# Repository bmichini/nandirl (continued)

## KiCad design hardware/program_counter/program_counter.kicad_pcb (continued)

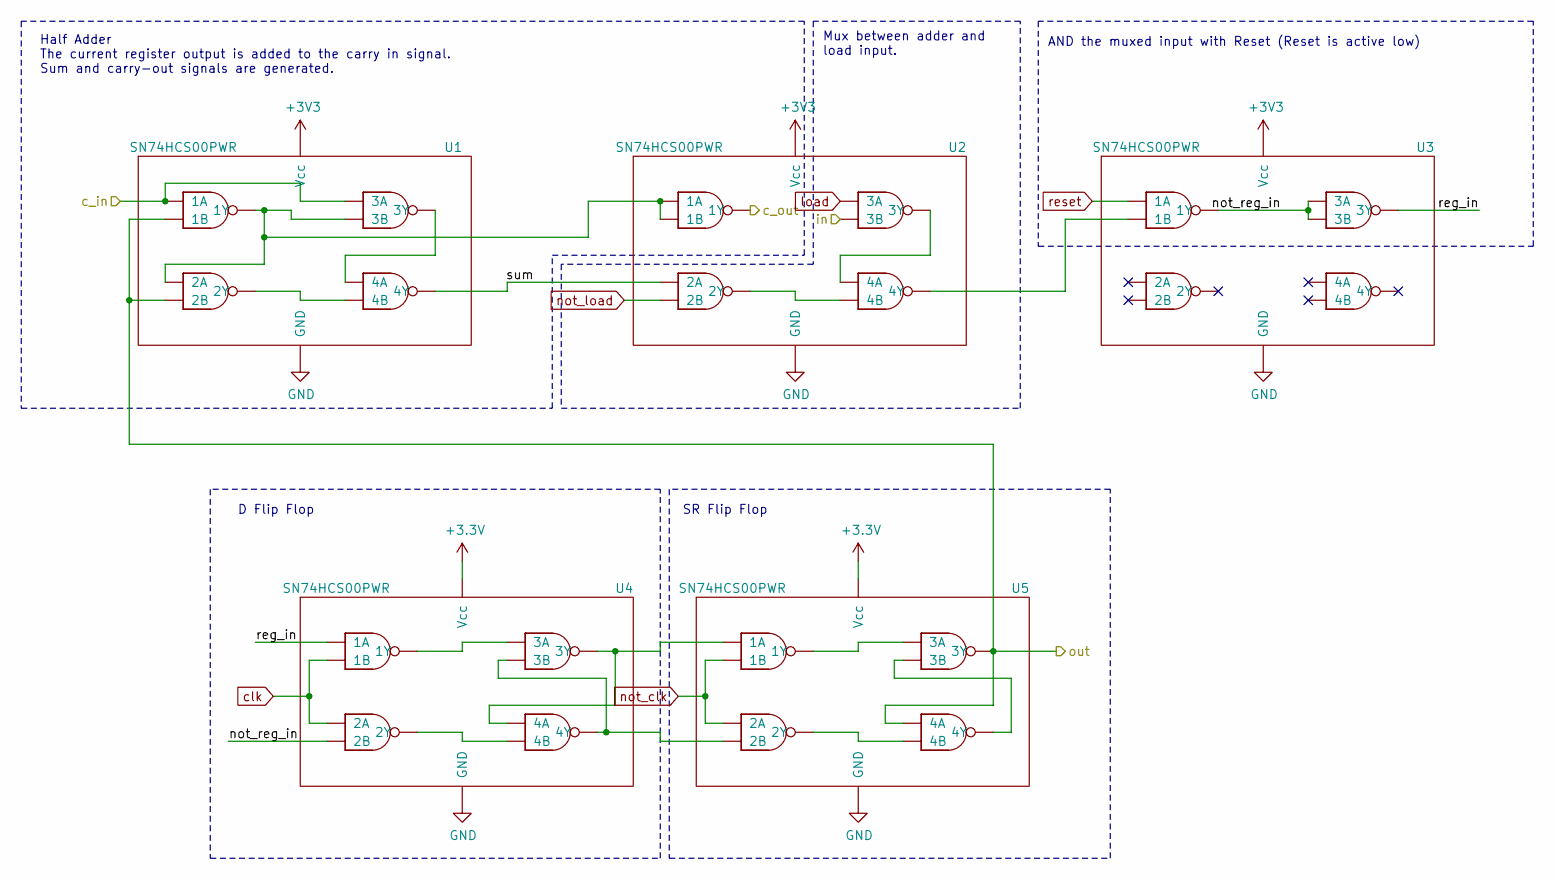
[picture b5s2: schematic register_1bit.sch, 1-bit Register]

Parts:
U1, U2, U3, U4, U5: SN74HCS00PWR; TSSOP-14_4.4x5mm_P0.65mm; Digikey PN 296-SN74HCS00PWRCT-ND

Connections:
/Bit 0/not_reg_in: U3.3 (1Y), U3.9 (3A), U3.10 (3B), U4.5 (2B)
/Bit 0/reg_in: U3.8 (3Y), U4.1 (1A)
/Bit 0/sum: U1.11 (4Y), U2.4 (2A)
/sheet5EB6EF30/c_in: U2.3 (1Y); also elsewhere on the board
GND: U1.7 (GND), U2.7 (GND), U3.7 (GND), U4.7 (GND), U5.7 (GND); also elsewhere on the board
unnamed: U1.3 (1Y), U1.4 (2A), U1.10 (3B), U2.1 (1A), U2.2 (1B)
unnamed: U1.8 (3Y), U1.12 (4A)
unnamed: U1.6 (2Y), U1.13 (4B)
unnamed: U2.11 (4Y), U3.2 (1B)
unnamed: U2.8 (3Y), U2.12 (4A)
unnamed: U2.6 (2Y), U2.13 (4B)
unnamed: U4.3 (1Y), U4.9 (3A)
unnamed: U4.10 (3B), U4.11 (4Y), U5.5 (2B)
unnamed: U4.8 (3Y), U4.12 (4A), U5.1 (1A)
unnamed: U4.6 (2Y), U4.13 (4B)
unnamed: U5.3 (1Y), U5.9 (3A)
unnamed: U5.10 (3B), U5.11 (4Y)
unnamed: U5.6 (2Y), U5.13 (4B)
clk: U4.2 (1B), U4.4 (2A); also elsewhere on the board
in0: U2.10 (3B); also elsewhere on the board
inc: U1.1 (1A), U1.9 (3A); also elsewhere on the board
load: U2.9 (3A); also elsewhere on the board
not_clk: U5.2 (1B), U5.4 (2A); also elsewhere on the board
not_load: U2.5 (2B); also elsewhere on the board
out0: U1.2 (1B), U1.5 (2B), U5.8 (3Y), U5.12 (4A); also elsewhere on the board
reset: U3.1 (1A); also elsewhere on the board

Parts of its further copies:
U6, U7, U8, U9, U10, U11, U12, U13, U14, U15, U16, U17, U18, U19, U20, U21, U22, U23, U24, U25, U26, U27, U28, U29, U30, U31, U32, U33, U34, U35, U36, U37, U38, U39, U40, U41, U42, U43, U44, U45, U46, U47, U48, U49, U50, U51, U52, U53, U54, U55, U56, U57, U58, U59, U60, U61, U62, U63, U64, U65, U66, U67, U68, U69, U70, U71, U72, U73, U74, U75: SN74HCS00PWR; TSSOP-14_4.4x5mm_P0.65mm; Digikey PN 296-SN74HCS00PWRCT-ND

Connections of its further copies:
/sheet5EB6EF30/c_in: U71.1 (1A), U71.9 (3A); also elsewhere on the board
/sheet5EB6EF30/not_reg_in: U73.3 (1Y), U73.9 (3A), U73.10 (3B), U74.5 (2B)
/sheet5EB6EF30/reg_in: U73.8 (3Y), U74.1 (1A)
/sheet5EB6EF30/sum: U71.11 (4Y), U72.4 (2A)
/sheet5EBCE384/c_in: U66.1 (1A), U66.9 (3A), U72.3 (1Y)
/sheet5EBCE384/not_reg_in: U68.3 (1Y), U68.9 (3A), U68.10 (3B), U69.5 (2B)
/sheet5EBCE384/reg_in: U68.8 (3Y), U69.1 (1A)
/sheet5EBCE384/sum: U66.11 (4Y), U67.4 (2A)
/sheet5EBD798B/c_in: U61.1 (1A), U61.9 (3A), U67.3 (1Y)
/sheet5EBD798B/not_reg_in: U63.3 (1Y), U63.9 (3A), U63.10 (3B), U64.5 (2B)
/sheet5EBD798B/reg_in: U63.8 (3Y), U64.1 (1A)
/sheet5EBD798B/sum: U61.11 (4Y), U62.4 (2A)
/sheet5EBD798C/c_in: U56.1 (1A), U56.9 (3A), U62.3 (1Y)
/sheet5EBD798C/not_reg_in: U58.3 (1Y), U58.9 (3A), U58.10 (3B), U59.5 (2B)
/sheet5EBD798C/reg_in: U58.8 (3Y), U59.1 (1A)
/sheet5EBD798C/sum: U56.11 (4Y), U57.4 (2A)
/sheet5EBF7D34/c_in: U51.1 (1A), U51.9 (3A), U57.3 (1Y)
/sheet5EBF7D34/not_reg_in: U53.3 (1Y), U53.9 (3A), U53.10 (3B), U54.5 (2B)
/sheet5EBF7D34/reg_in: U53.8 (3Y), U54.1 (1A)
/sheet5EBF7D34/sum: U51.11 (4Y), U52.4 (2A)
/sheet5EBF7D35/c_in: U46.1 (1A), U46.9 (3A), U52.3 (1Y)
/sheet5EBF7D35/not_reg_in: U48.3 (1Y), U48.9 (3A), U48.10 (3B), U49.5 (2B)
/sheet5EBF7D35/reg_in: U48.8 (3Y), U49.1 (1A)
/sheet5EBF7D35/sum: U46.11 (4Y), U47.4 (2A)
/sheet5EBF7D36/c_in: U41.1 (1A), U41.9 (3A), U47.3 (1Y)
/sheet5EBF7D36/not_reg_in: U43.3 (1Y), U43.9 (3A), U43.10 (3B), U44.5 (2B)
/sheet5EBF7D36/reg_in: U43.8 (3Y), U44.1 (1A)
/sheet5EBF7D36/sum: U41.11 (4Y), U42.4 (2A)
/sheet5EBF7D37/c_in: U36.1 (1A), U36.9 (3A), U42.3 (1Y)
/sheet5EBF7D37/not_reg_in: U38.3 (1Y), U38.9 (3A), U38.10 (3B), U39.5 (2B)
/sheet5EBF7D37/reg_in: U38.8 (3Y), U39.1 (1A)
/sheet5EBF7D37/sum: U36.11 (4Y), U37.4 (2A)
/sheet5EC1DCDE/c_in: U31.1 (1A), U31.9 (3A), U37.3 (1Y)
/sheet5EC1DCDE/not_reg_in: U33.3 (1Y), U33.9 (3A), U33.10 (3B), U34.5 (2B)
/sheet5EC1DCDE/reg_in: U33.8 (3Y), U34.1 (1A)
/sheet5EC1DCDE/sum: U31.11 (4Y), U32.4 (2A)
/sheet5EC1DCDF/c_in: U26.1 (1A), U26.9 (3A), U32.3 (1Y)
/sheet5EC1DCDF/not_reg_in: U28.3 (1Y), U28.9 (3A), U28.10 (3B), U29.5 (2B)
/sheet5EC1DCDF/reg_in: U28.8 (3Y), U29.1 (1A)
/sheet5EC1DCDF/sum: U26.11 (4Y), U27.4 (2A)
/sheet5EC1DCE0/c_in: U21.1 (1A), U21.9 (3A), U27.3 (1Y)
/sheet5EC1DCE0/not_reg_in: U23.3 (1Y), U23.9 (3A), U23.10 (3B), U24.5 (2B)
/sheet5EC1DCE0/reg_in: U23.8 (3Y), U24.1 (1A)
/sheet5EC1DCE0/sum: U21.11 (4Y), U22.4 (2A)
/sheet5EC1DCE1/c_in: U16.1 (1A), U16.9 (3A), U22.3 (1Y)
/sheet5EC1DCE1/not_reg_in: U18.3 (1Y), U18.9 (3A), U18.10 (3B), U19.5 (2B)
/sheet5EC1DCE1/reg_in: U18.8 (3Y), U19.1 (1A)
/sheet5EC1DCE1/sum: U16.11 (4Y), U17.4 (2A)
/sheet5EC1DCE2/c_in: U11.1 (1A), U11.9 (3A), U17.3 (1Y)
/sheet5EC1DCE2/not_reg_in: U13.3 (1Y), U13.9 (3A), U13.10 (3B), U14.5 (2B)
/sheet5EC1DCE2/reg_in: U13.8 (3Y), U14.1 (1A)
/sheet5EC1DCE2/sum: U11.11 (4Y), U12.4 (2A)
/sheet5EC1DCE3/c_in: U6.1 (1A), U6.9 (3A), U12.3 (1Y)
/sheet5EC1DCE3/c_out: U7.3 (1Y)
/sheet5EC1DCE3/not_reg_in: U8.3 (1Y), U8.9 (3A), U8.10 (3B), U9.5 (2B)
/sheet5EC1DCE3/reg_in: U8.8 (3Y), U9.1 (1A)
/sheet5EC1DCE3/sum: U6.11 (4Y), U7.4 (2A)
GND: U6.7 (GND), U7.7 (GND), U8.7 (GND), U9.7 (GND), U10.7 (GND), U11.7 (GND), U12.7 (GND), U13.7 (GND), U14.7 (GND), U15.7 (GND), U16.7 (GND), U17.7 (GND), U18.7 (GND), U19.7 (GND), U20.7 (GND), U21.7 (GND), U22.7 (GND), U23.7 (GND), U24.7 (GND), U25.7 (GND), U26.7 (GND), U27.7 (GND), U28.7 (GND), U29.7 (GND), U30.7 (GND), U31.7 (GND), U32.7 (GND), U33.7 (GND), U34.7 (GND), U35.7 (GND), U36.7 (GND), U37.7 (GND), U38.7 (GND), U39.7 (GND), U40.7 (GND), U41.7 (GND), U42.7 (GND), U43.7 (GND), U44.7 (GND), U45.7 (GND), U46.7 (GND), U47.7 (GND), U48.7 (GND), U49.7 (GND), U50.7 (GND), U51.7 (GND), U52.7 (GND), U53.7 (GND), U54.7 (GND), U55.7 (GND), U56.7 (GND), U57.7 (GND), U58.7 (GND), U59.7 (GND), U60.7 (GND), U61.7 (GND), U62.7 (GND), U63.7 (GND), U64.7 (GND), U65.7 (GND), U66.7 (GND), U67.7 (GND), U68.7 (GND), U69.7 (GND), U70.7 (GND), U71.7 (GND), U72.7 (GND), U73.7 (GND), U74.7 (GND), U75.7 (GND); also elsewhere on the board
unnamed: U6.3 (1Y), U6.4 (2A), U6.10 (3B), U7.1 (1A), U7.2 (1B)
unnamed: U6.8 (3Y), U6.12 (4A)
unnamed: U6.6 (2Y), U6.13 (4B)
unnamed: U7.11 (4Y), U8.2 (1B)
unnamed: U7.8 (3Y), U7.12 (4A)
unnamed: U7.6 (2Y), U7.13 (4B)
unnamed: U9.3 (1Y), U9.9 (3A)
unnamed: U9.6 (2Y), U9.13 (4B)
unnamed: U9.8 (3Y), U9.12 (4A), U10.1 (1A)
unnamed: U10.3 (1Y), U10.9 (3A)
unnamed: U9.10 (3B), U9.11 (4Y), U10.5 (2B)
unnamed: U10.10 (3B), U10.11 (4Y)
unnamed: U10.6 (2Y), U10.13 (4B)
unnamed: U11.3 (1Y), U11.4 (2A), U11.10 (3B), U12.1 (1A), U12.2 (1B)
unnamed: U11.8 (3Y), U11.12 (4A)
unnamed: U11.6 (2Y), U11.13 (4B)
unnamed: U12.11 (4Y), U13.2 (1B)
unnamed: U12.8 (3Y), U12.12 (4A)
unnamed: U12.6 (2Y), U12.13 (4B)
unnamed: U14.3 (1Y), U14.9 (3A)
unnamed: U14.10 (3B), U14.11 (4Y), U15.5 (2B)
unnamed: U14.8 (3Y), U14.12 (4A), U15.1 (1A)
unnamed: U14.6 (2Y), U14.13 (4B)
unnamed: U15.3 (1Y), U15.9 (3A)
unnamed: U15.10 (3B), U15.11 (4Y)
unnamed: U15.6 (2Y), U15.13 (4B)
unnamed: U16.3 (1Y), U16.4 (2A), U16.10 (3B), U17.1 (1A), U17.2 (1B)
unnamed: U16.8 (3Y), U16.12 (4A)
unnamed: U16.6 (2Y), U16.13 (4B)
unnamed: U17.11 (4Y), U18.2 (1B)
unnamed: U17.8 (3Y), U17.12 (4A)
unnamed: U17.6 (2Y), U17.13 (4B)
unnamed: U19.3 (1Y), U19.9 (3A)
unnamed: U19.10 (3B), U19.11 (4Y), U20.5 (2B)
unnamed: U19.8 (3Y), U19.12 (4A), U20.1 (1A)
unnamed: U19.6 (2Y), U19.13 (4B)
unnamed: U20.3 (1Y), U20.9 (3A)
unnamed: U20.10 (3B), U20.11 (4Y)
unnamed: U20.6 (2Y), U20.13 (4B)
unnamed: U21.3 (1Y), U21.4 (2A), U21.10 (3B), U22.1 (1A), U22.2 (1B)
unnamed: U21.8 (3Y), U21.12 (4A)
unnamed: U21.6 (2Y), U21.13 (4B)
unnamed: U22.11 (4Y), U23.2 (1B)
unnamed: U22.8 (3Y), U22.12 (4A)
unnamed: U22.6 (2Y), U22.13 (4B)
unnamed: U24.3 (1Y), U24.9 (3A)
unnamed: U24.10 (3B), U24.11 (4Y), U25.5 (2B)
unnamed: U24.8 (3Y), U24.12 (4A), U25.1 (1A)
unnamed: U24.6 (2Y), U24.13 (4B)
unnamed: U25.3 (1Y), U25.9 (3A)
unnamed: U25.10 (3B), U25.11 (4Y)
unnamed: U25.6 (2Y), U25.13 (4B)
unnamed: U26.3 (1Y), U26.4 (2A), U26.10 (3B), U27.1 (1A), U27.2 (1B)
unnamed: U26.8 (3Y), U26.12 (4A)
unnamed: U26.6 (2Y), U26.13 (4B)
unnamed: U27.11 (4Y), U28.2 (1B)
unnamed: U27.8 (3Y), U27.12 (4A)
unnamed: U27.6 (2Y), U27.13 (4B)
unnamed: U29.3 (1Y), U29.9 (3A)
unnamed: U29.10 (3B), U29.11 (4Y), U30.5 (2B)
unnamed: U29.8 (3Y), U29.12 (4A), U30.1 (1A)
unnamed: U29.6 (2Y), U29.13 (4B)
unnamed: U30.3 (1Y), U30.9 (3A)
unnamed: U30.10 (3B), U30.11 (4Y)
unnamed: U30.6 (2Y), U30.13 (4B)
unnamed: U31.3 (1Y), U31.4 (2A), U31.10 (3B), U32.1 (1A), U32.2 (1B)
unnamed: U31.8 (3Y), U31.12 (4A)
unnamed: U31.6 (2Y), U31.13 (4B)
unnamed: U32.11 (4Y), U33.2 (1B)
unnamed: U32.8 (3Y), U32.12 (4A)
unnamed: U32.6 (2Y), U32.13 (4B)
unnamed: U34.3 (1Y), U34.9 (3A)
unnamed: U34.10 (3B), U34.11 (4Y), U35.5 (2B)
unnamed: U34.8 (3Y), U34.12 (4A), U35.1 (1A)
unnamed: U34.6 (2Y), U34.13 (4B)
unnamed: U35.3 (1Y), U35.9 (3A)
unnamed: U35.10 (3B), U35.11 (4Y)
unnamed: U35.6 (2Y), U35.13 (4B)
unnamed: U36.3 (1Y), U36.4 (2A), U36.10 (3B), U37.1 (1A), U37.2 (1B)
unnamed: U36.8 (3Y), U36.12 (4A)
unnamed: U36.6 (2Y), U36.13 (4B)
unnamed: U37.11 (4Y), U38.2 (1B)
unnamed: U37.8 (3Y), U37.12 (4A)
unnamed: U37.6 (2Y), U37.13 (4B)
unnamed: U39.3 (1Y), U39.9 (3A)
unnamed: U39.10 (3B), U39.11 (4Y), U40.5 (2B)
unnamed: U39.8 (3Y), U39.12 (4A), U40.1 (1A)
unnamed: U39.6 (2Y), U39.13 (4B)
unnamed: U40.3 (1Y), U40.9 (3A)
unnamed: U40.10 (3B), U40.11 (4Y)
unnamed: U40.6 (2Y), U40.13 (4B)
unnamed: U41.3 (1Y), U41.4 (2A), U41.10 (3B), U42.1 (1A), U42.2 (1B)
unnamed: U41.8 (3Y), U41.12 (4A)
unnamed: U41.6 (2Y), U41.13 (4B)
unnamed: U42.11 (4Y), U43.2 (1B)
unnamed: U42.8 (3Y), U42.12 (4A)
unnamed: U42.6 (2Y), U42.13 (4B)
unnamed: U44.3 (1Y), U44.9 (3A)
unnamed: U44.10 (3B), U44.11 (4Y), U45.5 (2B)
unnamed: U44.8 (3Y), U44.12 (4A), U45.1 (1A)
unnamed: U44.6 (2Y), U44.13 (4B)
unnamed: U45.3 (1Y), U45.9 (3A)
unnamed: U45.10 (3B), U45.11 (4Y)
unnamed: U45.6 (2Y), U45.13 (4B)
unnamed: U46.3 (1Y), U46.4 (2A), U46.10 (3B), U47.1 (1A), U47.2 (1B)
unnamed: U46.8 (3Y), U46.12 (4A)
unnamed: U46.6 (2Y), U46.13 (4B)
unnamed: U47.11 (4Y), U48.2 (1B)
unnamed: U47.8 (3Y), U47.12 (4A)
unnamed: U47.6 (2Y), U47.13 (4B)
unnamed: U49.3 (1Y), U49.9 (3A)
unnamed: U49.10 (3B), U49.11 (4Y), U50.5 (2B)
unnamed: U49.8 (3Y), U49.12 (4A), U50.1 (1A)
unnamed: U49.6 (2Y), U49.13 (4B)
unnamed: U50.3 (1Y), U50.9 (3A)
unnamed: U50.10 (3B), U50.11 (4Y)
unnamed: U50.6 (2Y), U50.13 (4B)
unnamed: U51.3 (1Y), U51.4 (2A), U51.10 (3B), U52.1 (1A), U52.2 (1B)
unnamed: U51.8 (3Y), U51.12 (4A)
unnamed: U51.6 (2Y), U51.13 (4B)
unnamed: U52.11 (4Y), U53.2 (1B)
unnamed: U52.8 (3Y), U52.12 (4A)
unnamed: U52.6 (2Y), U52.13 (4B)
unnamed: U54.3 (1Y), U54.9 (3A)
unnamed: U54.10 (3B), U54.11 (4Y), U55.5 (2B)
unnamed: U54.8 (3Y), U54.12 (4A), U55.1 (1A)
unnamed: U54.6 (2Y), U54.13 (4B)
unnamed: U55.3 (1Y), U55.9 (3A)
unnamed: U55.10 (3B), U55.11 (4Y)
unnamed: U55.6 (2Y), U55.13 (4B)
unnamed: U56.3 (1Y), U56.4 (2A), U56.10 (3B), U57.1 (1A), U57.2 (1B)
unnamed: U56.8 (3Y), U56.12 (4A)
unnamed: U56.6 (2Y), U56.13 (4B)
unnamed: U57.11 (4Y), U58.2 (1B)
unnamed: U57.8 (3Y), U57.12 (4A)
unnamed: U57.6 (2Y), U57.13 (4B)
unnamed: U59.3 (1Y), U59.9 (3A)
unnamed: U59.10 (3B), U59.11 (4Y), U60.5 (2B)
unnamed: U59.8 (3Y), U59.12 (4A), U60.1 (1A)
unnamed: U59.6 (2Y), U59.13 (4B)
unnamed: U60.3 (1Y), U60.9 (3A)
unnamed: U60.10 (3B), U60.11 (4Y)
unnamed: U60.6 (2Y), U60.13 (4B)
unnamed: U61.3 (1Y), U61.4 (2A), U61.10 (3B), U62.1 (1A), U62.2 (1B)
unnamed: U61.8 (3Y), U61.12 (4A)
unnamed: U61.6 (2Y), U61.13 (4B)
unnamed: U62.11 (4Y), U63.2 (1B)
unnamed: U62.8 (3Y), U62.12 (4A)
unnamed: U62.6 (2Y), U62.13 (4B)
unnamed: U64.3 (1Y), U64.9 (3A)
unnamed: U64.10 (3B), U64.11 (4Y), U65.5 (2B)
unnamed: U64.8 (3Y), U64.12 (4A), U65.1 (1A)
unnamed: U64.6 (2Y), U64.13 (4B)
unnamed: U65.3 (1Y), U65.9 (3A)
unnamed: U65.10 (3B), U65.11 (4Y)
unnamed: U65.6 (2Y), U65.13 (4B)
unnamed: U66.3 (1Y), U66.4 (2A), U66.10 (3B), U67.1 (1A), U67.2 (1B)
unnamed: U66.8 (3Y), U66.12 (4A)
unnamed: U66.6 (2Y), U66.13 (4B)
unnamed: U67.11 (4Y), U68.2 (1B)
unnamed: U67.8 (3Y), U67.12 (4A)
unnamed: U67.6 (2Y), U67.13 (4B)
unnamed: U69.3 (1Y), U69.9 (3A)
unnamed: U69.10 (3B), U69.11 (4Y), U70.5 (2B)
unnamed: U69.8 (3Y), U69.12 (4A), U70.1 (1A)
unnamed: U69.6 (2Y), U69.13 (4B)
unnamed: U70.3 (1Y), U70.9 (3A)
unnamed: U70.10 (3B), U70.11 (4Y)
unnamed: U70.6 (2Y), U70.13 (4B)
unnamed: U71.3 (1Y), U71.4 (2A), U71.10 (3B), U72.1 (1A), U72.2 (1B)
unnamed: U71.8 (3Y), U71.12 (4A)
unnamed: U71.6 (2Y), U71.13 (4B)
unnamed: U72.11 (4Y), U73.2 (1B)
unnamed: U72.8 (3Y), U72.12 (4A)
unnamed: U72.6 (2Y), U72.13 (4B)
unnamed: U74.3 (1Y), U74.9 (3A)
unnamed: U74.10 (3B), U74.11 (4Y), U75.5 (2B)
unnamed: U74.8 (3Y), U74.12 (4A), U75.1 (1A)
unnamed: U74.6 (2Y), U74.13 (4B)
unnamed: U75.3 (1Y), U75.9 (3A)
unnamed: U75.10 (3B), U75.11 (4Y)
unnamed: U75.6 (2Y), U75.13 (4B)
clk: U9.2 (1B), U9.4 (2A), U14.2 (1B), U14.4 (2A), U19.2 (1B), U19.4 (2A), U24.2 (1B), U24.4 (2A), U29.2 (1B), U29.4 (2A), U34.2 (1B), U34.4 (2A), U39.2 (1B), U39.4 (2A), U44.2 (1B), U44.4 (2A), U49.2 (1B), U49.4 (2A), U54.2 (1B), U54.4 (2A), U59.2 (1B), U59.4 (2A), U64.2 (1B), U64.4 (2A), U69.2 (1B), U69.4 (2A), U74.2 (1B), U74.4 (2A); also elsewhere on the board
in1: U72.10 (3B); also elsewhere on the board
in2: U67.10 (3B); also elsewhere on the board
in3: U62.10 (3B); also elsewhere on the board
in4: U57.10 (3B); also elsewhere on the board
in5: U52.10 (3B); also elsewhere on the board
in6: U47.10 (3B); also elsewhere on the board
in7: U42.10 (3B); also elsewhere on the board
in8: U37.10 (3B); also elsewhere on the board
in9: U32.10 (3B); also elsewhere on the board
in10: U27.10 (3B); also elsewhere on the board
in11: U22.10 (3B); also elsewhere on the board
in12: U17.10 (3B); also elsewhere on the board
in13: U12.10 (3B); also elsewhere on the board
in14: U7.10 (3B); also elsewhere on the board
load: U7.9 (3A), U12.9 (3A), U17.9 (3A), U22.9 (3A), U27.9 (3A), U32.9 (3A), U37.9 (3A), U42.9 (3A), U47.9 (3A), U52.9 (3A), U57.9 (3A), U62.9 (3A), U67.9 (3A), U72.9 (3A); also elsewhere on the board
not_clk: U10.2 (1B), U10.4 (2A), U15.2 (1B), U15.4 (2A), U20.2 (1B), U20.4 (2A), U25.2 (1B), U25.4 (2A), U30.2 (1B), U30.4 (2A), U35.2 (1B), U35.4 (2A), U40.2 (1B), U40.4 (2A), U45.2 (1B), U45.4 (2A), U50.2 (1B), U50.4 (2A), U55.2 (1B), U55.4 (2A), U60.2 (1B), U60.4 (2A), U65.2 (1B), U65.4 (2A), U70.2 (1B), U70.4 (2A), U75.2 (1B), U75.4 (2A); also elsewhere on the board
not_load: U7.5 (2B), U12.5 (2B), U17.5 (2B), U22.5 (2B), U27.5 (2B), U32.5 (2B), U37.5 (2B), U42.5 (2B), U47.5 (2B), U52.5 (2B), U57.5 (2B), U62.5 (2B), U67.5 (2B), U72.5 (2B); also elsewhere on the board
out1: U71.2 (1B), U71.5 (2B), U75.8 (3Y), U75.12 (4A); also elsewhere on the board
out2: U66.2 (1B), U66.5 (2B), U70.8 (3Y), U70.12 (4A); also elsewhere on the board
out3: U61.2 (1B), U61.5 (2B), U65.8 (3Y), U65.12 (4A); also elsewhere on the board
out4: U56.2 (1B), U56.5 (2B), U60.8 (3Y), U60.12 (4A); also elsewhere on the board
out5: U51.2 (1B), U51.5 (2B), U55.8 (3Y), U55.12 (4A); also elsewhere on the board
out6: U46.2 (1B), U46.5 (2B), U50.8 (3Y), U50.12 (4A); also elsewhere on the board
out7: U41.2 (1B), U41.5 (2B), U45.8 (3Y), U45.12 (4A); also elsewhere on the board
out8: U36.2 (1B), U36.5 (2B), U40.8 (3Y), U40.12 (4A); also elsewhere on the board
out9: U31.2 (1B), U31.5 (2B), U35.8 (3Y), U35.12 (4A); also elsewhere on the board
out10: U26.2 (1B), U26.5 (2B), U30.8 (3Y), U30.12 (4A); also elsewhere on the board
out11: U21.2 (1B), U21.5 (2B), U25.8 (3Y), U25.12 (4A); also elsewhere on the board
out12: U16.2 (1B), U16.5 (2B), U20.8 (3Y), U20.12 (4A); also elsewhere on the board
out13: U11.2 (1B), U11.5 (2B), U15.8 (3Y), U15.12 (4A); also elsewhere on the board
out14: U6.2 (1B), U6.5 (2B), U10.8 (3Y), U10.12 (4A); also elsewhere on the board
reset: U8.1 (1A), U13.1 (1A), U18.1 (1A), U23.1 (1A), U28.1 (1A), U33.1 (1A), U38.1 (1A), U43.1 (1A), U48.1 (1A), U53.1 (1A), U58.1 (1A), U63.1 (1A), U68.1 (1A), U73.1 (1A); also elsewhere on the board

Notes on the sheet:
D Flip Flop
SR Flip Flop
Half Adder The current register output is added to the carry in signal. Sum and carry-out signals are generated.
Mux between adder and load input.
AND the muxed input with Reset (Reset is active low)

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
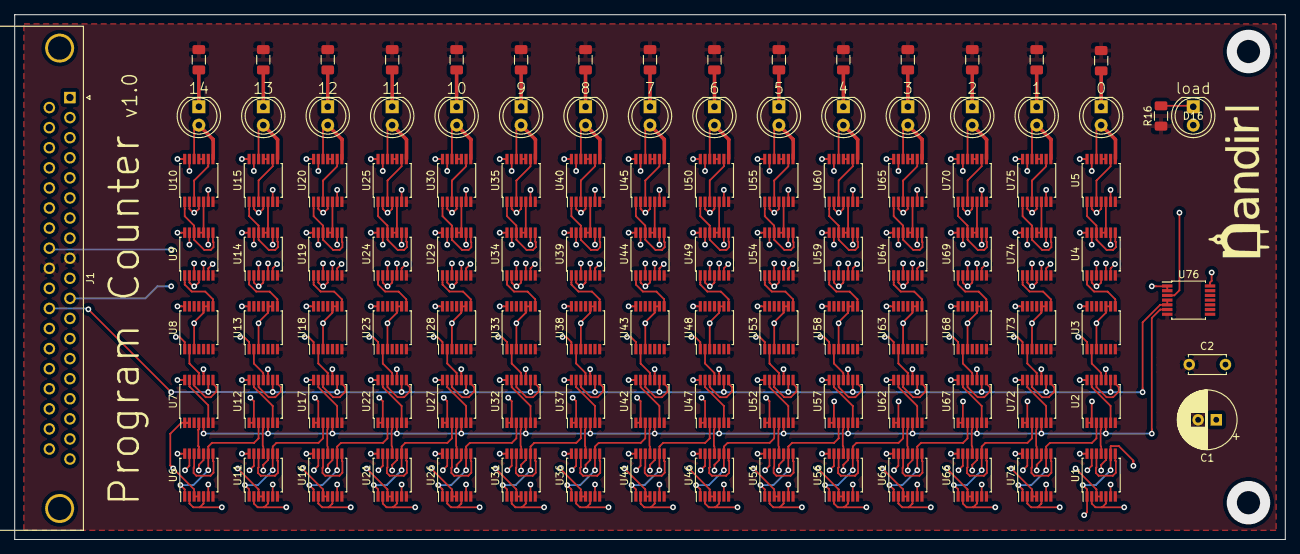
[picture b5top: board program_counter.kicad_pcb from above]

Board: 4 copper layers, 175.3 x 72.4 mm, 111 parts (0 on the bottom side), 308 nets.

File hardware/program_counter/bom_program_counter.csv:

Reference, Quantity, Value, Footprint, Datasheet, Digikey PN
C1 ,1,"100uF","Capacitor_THT:CP_Radial_D8.0mm_P2.50mm","~","P15797CT-ND"
C2 ,1,"100nF","Capacitor_THT:C_Disc_D5.0mm_W2.5mm_P5.00mm","~","BC5229CT-ND"
D15 D14 D13 D12 D11 D10 D9 D8 D7 D6 D5 D4 D3 D1 D2 D16 ,16,"LED","LED_THT:LED_D5.0mm","~"
J1 ,1,"DB37_Male","Connector_Dsub:DSUB-37_Male_Horizontal_P2.77x2.84mm_EdgePinOffset7.70mm_Housed_MountingHolesOffset9.12mm"," ~","AE10986-ND"
R16 R1 R2 R3 R4 R5 R6 R7 R8 R9 R10 R11 R12 R13 R14 R15 ,16,"1K","Resistor_SMD:R_1206_3216Metric","~","P1.0KECT-ND"
U76 U10 U9 U8 U7 U6 U15 U14 U13 U12 U11 U20 U19 U18 U17 U16 U25 U24 U23 U22 U21 U30 U29 U28 U27 U26 U35 U34 U33 U32 U31 U40 U39 U38 U37 U36 U45 U44 U43 U42 U41 U50 U49 U48 U47 U46 U55 U54 U53 U52 U51 U60 U59 U58 U57 U56 U65 U64 U63 U62 U61 U70 U69 U68 U67 U66 U5 U4 U3 U2 U1 U75 U74 U73 U72 U71 ,76,"SN74HCS00PWR","Package_SO:TSSOP-14_4.4x5mm_P0.65mm","","296-SN74HCS00PWRCT-ND"

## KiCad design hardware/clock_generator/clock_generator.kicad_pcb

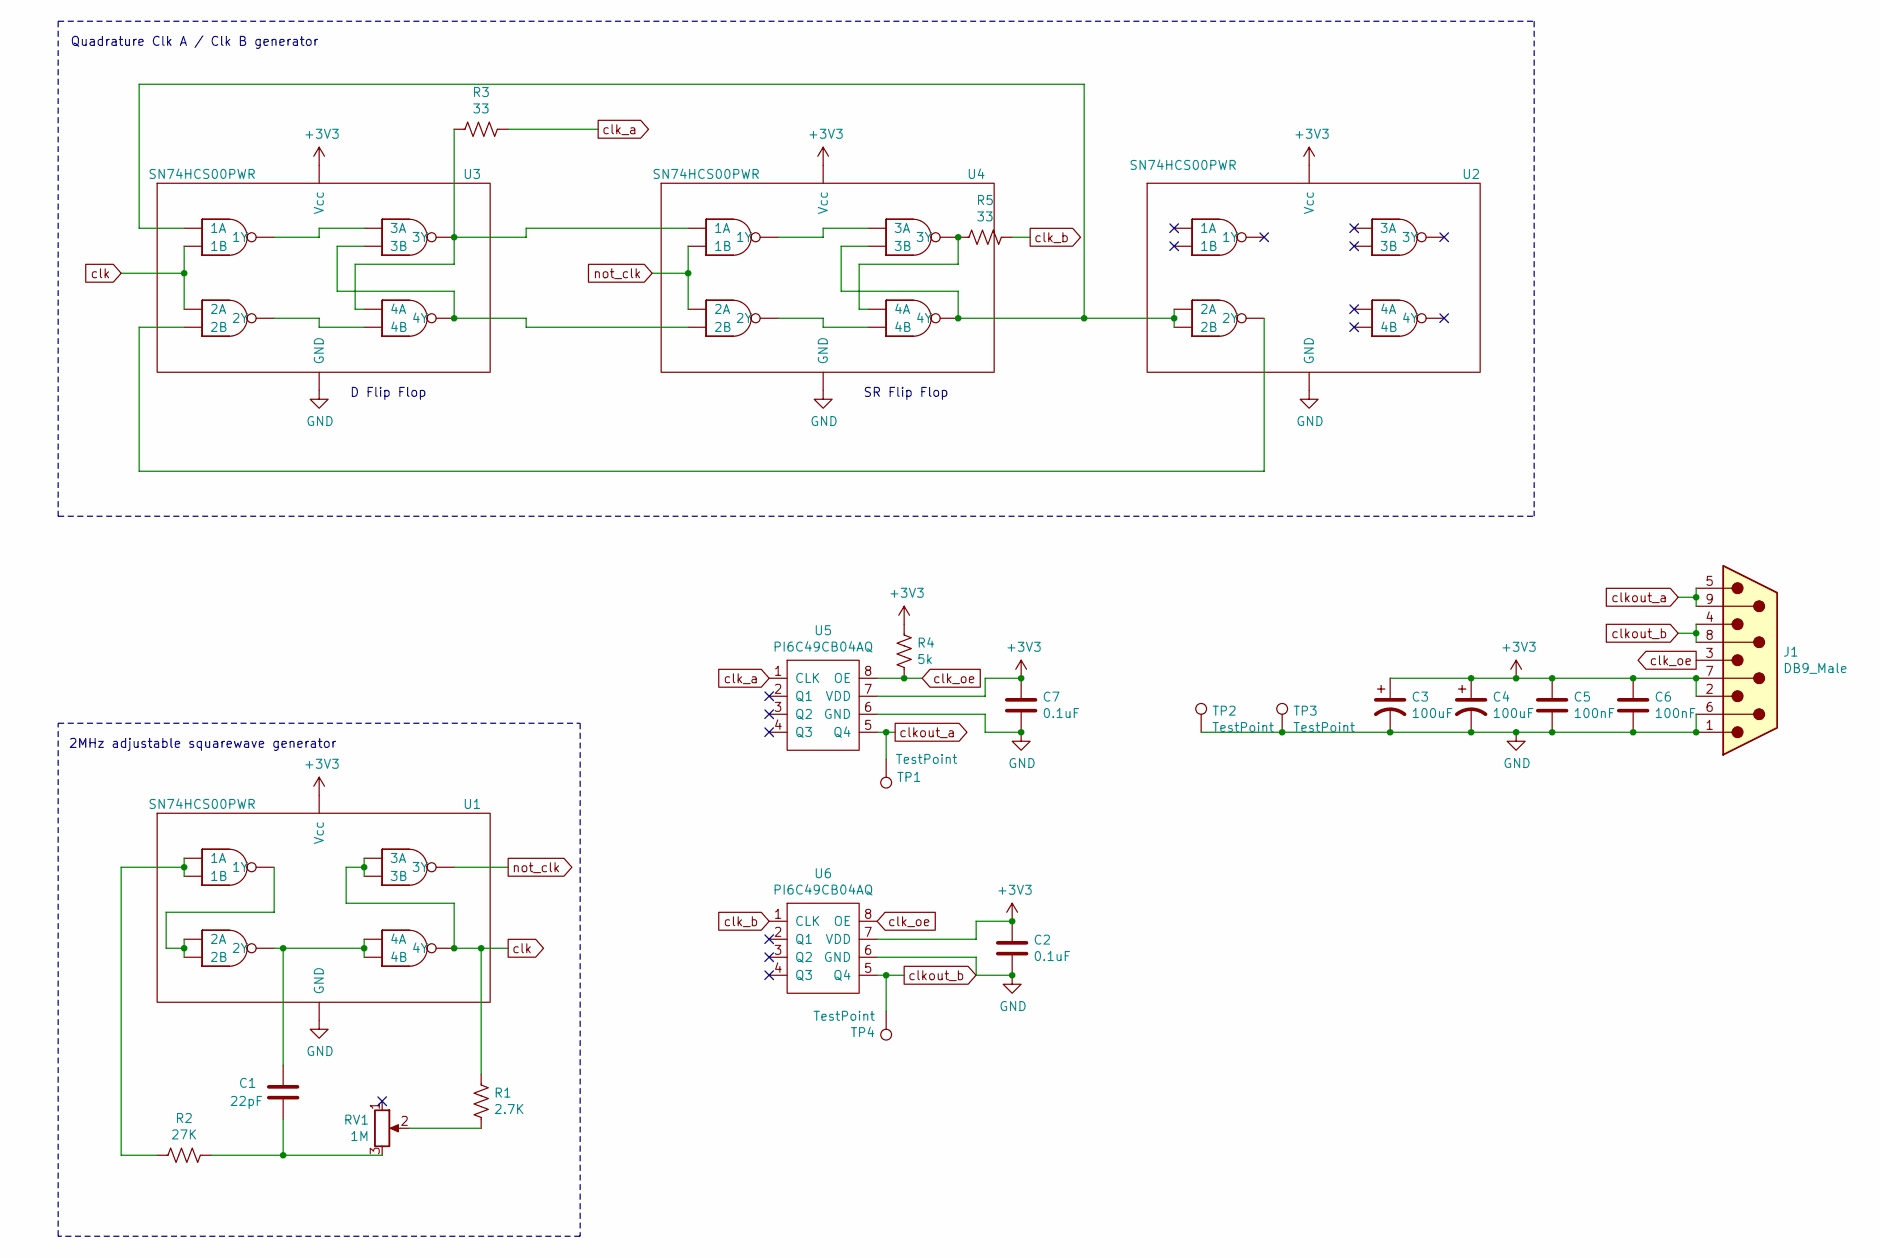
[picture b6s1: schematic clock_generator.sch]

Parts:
C1: 22pF; C_Disc_D5.0mm_W2.5mm_P5.00mm
C2, C7: 0.1uF; C_1206_3216Metric; Digikey PN 399-C1206C104K5RAC7800CT-ND
C3, C4: 100uF; CP_Radial_D8.0mm_P2.50mm; Digikey PN P15797CT-ND
C5, C6: 100nF; C_Disc_D5.0mm_W2.5mm_P5.00mm; Digikey PN BC5229CT-ND
J1: DB9_Male; DSUB-9_Male_Horizontal_P2.77x2.84mm_EdgePinOffset7.70mm_Hou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; Digikey PN AE10968-ND
R1: 2.7K; R_Axial_DIN0207_L6.3mm_D2.5mm_P10.16mm_Horizontal
R2: 27K; R_Axial_DIN0207_L6.3mm_D2.5mm_P10.16mm_Horizontal
R3, R5: 33; R_1206_3216Metric; Digikey PN P33ECT-ND
R4: 5k; R_1206_3216Metric; Digikey PN P5.1KECT-ND
RV1: 1M; Potentiometer_Bourns_PTV09A-1_Single_Vertical; Digikey PN PTV09A-4225F-B104-ND
TP1, TP2, TP3, TP4: TestPoint; TestPoint_Bridge_Pitch2.54mm_Drill1.0mm
U1, U2, U3, U4: SN74HCS00PWR; TSSOP-14_4.4x5mm_P0.65mm; Digikey PN 296-SN74HCS00PWRCT-ND
U5, U6: PI6C49CB04AQ; SOIC-8_3.9x4.9mm_P1.27mm; Digikey PN 31-PI6C49CB04AQ2WEXCT-ND

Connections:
+3V3: C2.1, C3.1, C4.1, C5.1, C6.1, C7.1, J1.2, J1.7, R4.2, U1.14 (Vcc), U2.14 (Vcc), U3.14 (Vcc), U4.14 (Vcc), U5.7 (VDD), U6.7 (VDD)
GND: C2.2, C3.2, C4.2, C5.2, C6.2, C7.2, J1.1, J1.6, TP2.1, TP3.1, U1.7 (GND), U2.7 (GND), U3.7 (GND), U4.7 (GND), U5.6 (GND), U6.6 (GND)
unnamed: C1.1, U1.6 (2Y), U1.12 (4A), U1.13 (4B)
unnamed: C1.2, R2.1, RV1.3
unnamed: R1.2, RV1.2
unnamed: R2.2, U1.1 (1A), U1.2 (1B)
unnamed: R3.2, U3.8 (3Y), U3.12 (4A), U4.1 (1A)
unnamed: R5.2, U4.8 (3Y), U4.12 (4A)
unnamed: U1.3 (1Y), U1.4 (2A), U1.5 (2B)
unnamed: U2.4 (2A), U2.5 (2B), U3.1 (1A), U4.10 (3B), U4.11 (4Y)
unnamed: U2.6 (2Y), U3.5 (2B)
unnamed: U3.3 (1Y), U3.9 (3A)
unnamed: U3.10 (3B), U3.11 (4Y), U4.5 (2B)
unnamed: U3.6 (2Y), U3.13 (4B)
unnamed: U4.3 (1Y), U4.9 (3A)
unnamed: U4.6 (2Y), U4.13 (4B)
clk: R1.1, U1.9 (3A), U1.10 (3B), U1.11 (4Y), U3.2 (1B), U3.4 (2A)
clk_a: R3.1, U5.1 (CLK)
clk_b: R5.1, U6.1 (CLK)
clk_oe: J1.3, R4.1, U5.8 (OE), U6.8 (OE)
clkout_a: J1.5, J1.9, TP1.1, U5.5 (Q4)
clkout_b: J1.4, J1.8, TP4.1, U6.5 (Q4)
not_clk: U1.8 (3Y), U4.2 (1B), U4.4 (2A)

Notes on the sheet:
2MHz adjustable squarewave generator
Quadrature Clk A / Clk B generator
D Flip Flop
SR Flip Flop

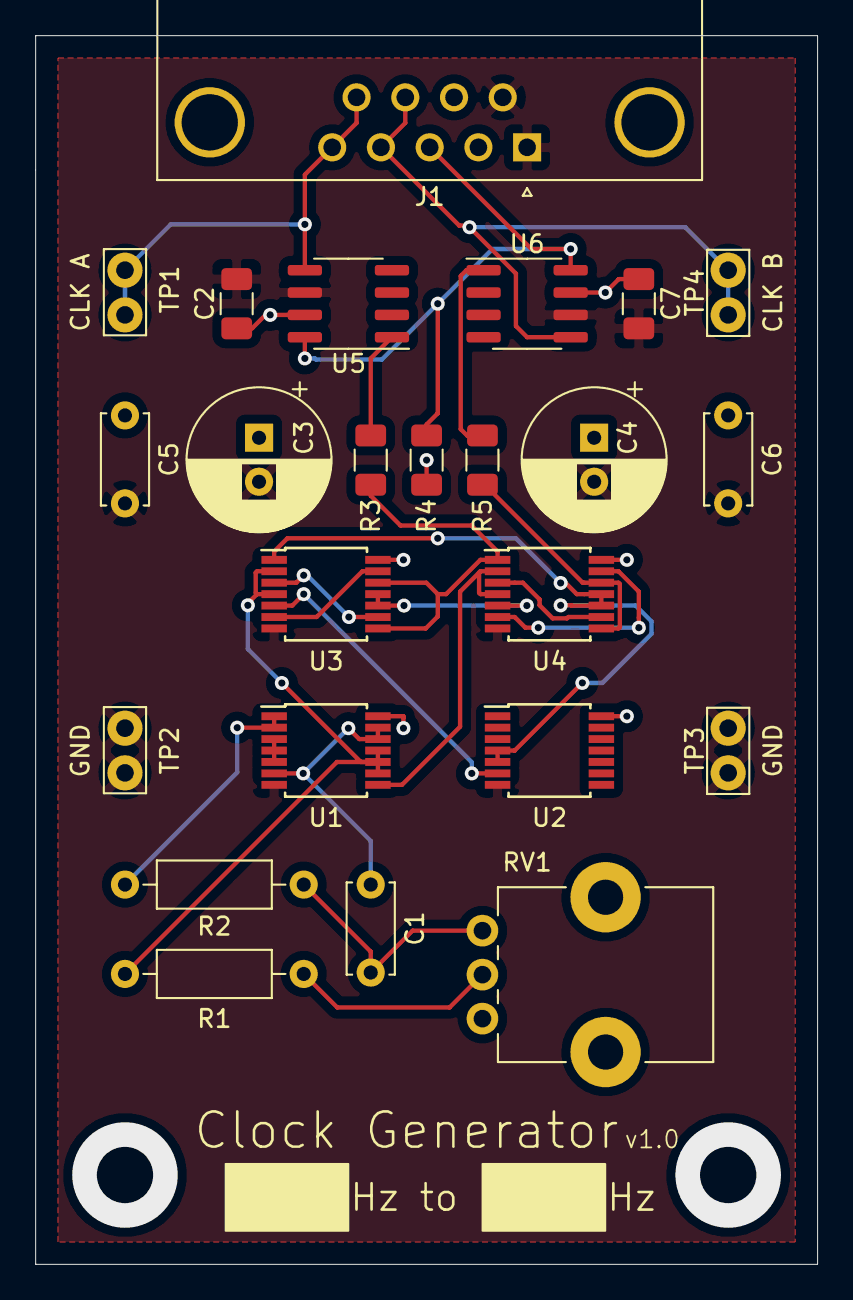
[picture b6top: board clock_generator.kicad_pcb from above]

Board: 2 copper layers, 44.4 x 69.8 mm, 24 parts (0 on the bottom side), 23 nets.

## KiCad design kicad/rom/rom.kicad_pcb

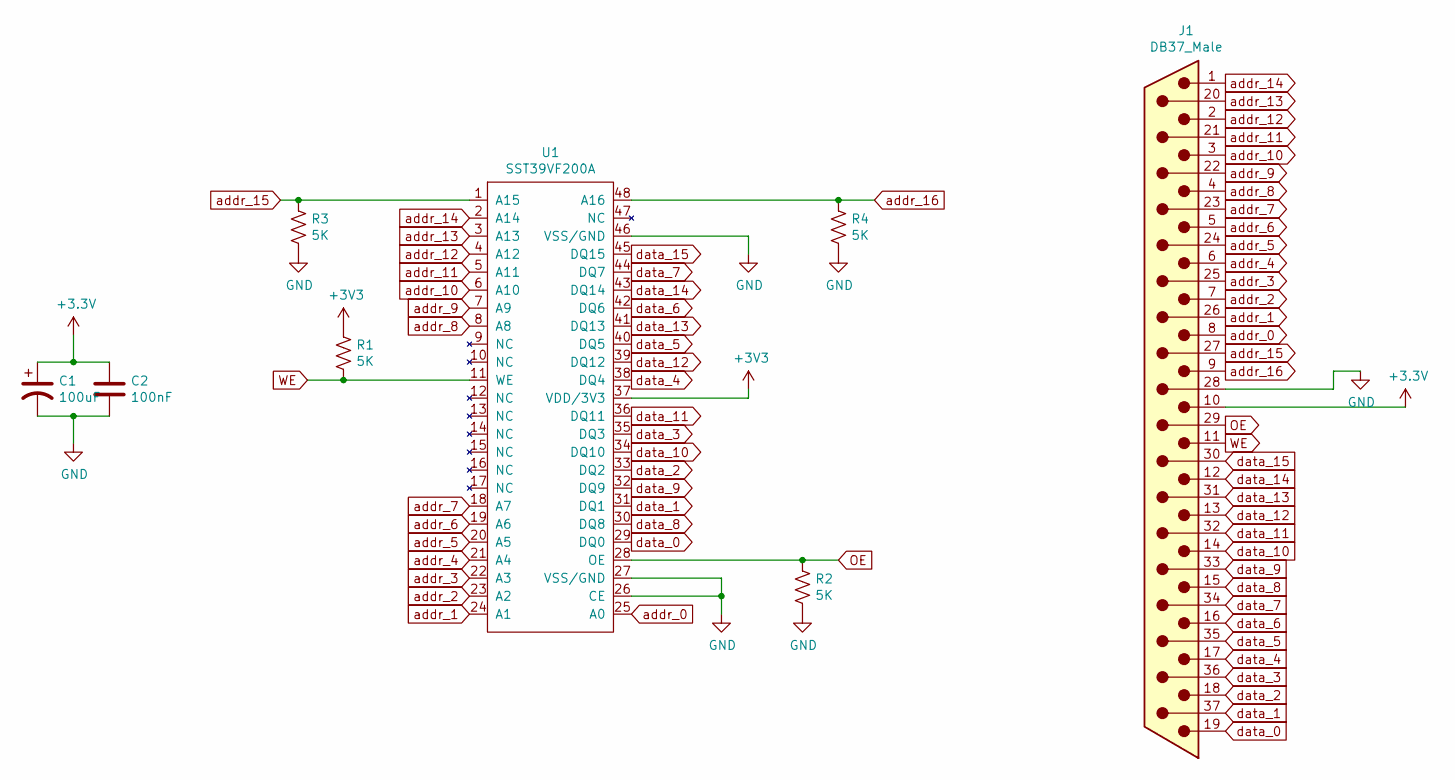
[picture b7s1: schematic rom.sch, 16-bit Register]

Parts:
C1: 100uF; CP_Radial_D8.0mm_P2.50mm; Digikey PN P15797CT-ND
C2: 100nF; C_Disc_D5.0mm_W2.5mm_P5.00mm; Digikey PN BC5229CT-ND
J1: DB37_Male; DSUB-37_Male_Horizontal_P2.77x2.84mm_EdgePinOffset7.70mm_Ho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; Digikey PN AE10986-ND
R1, R2, R3, R4: 5K; R_1206_3216Metric; Digikey PN P5.1KECT-ND
U1: SST39VF200A; TSOP-I-48_18.4x12mm_P0.5mm; Digikey PN SST39VF200A-70-4I-EKE-ND

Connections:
GND: C1.2, C2.2, J1.28, R2.2, R3.2, R4.2, U1.26 (CE), U1.27 (VSS/GND), U1.46 (VSS/GND)
OE: J1.29, R2.1, U1.28 (OE)
WE: J1.11, R1.2, U1.11 (WE)
addr_0: J1.8, U1.25 (A0)
addr_1: J1.26, U1.24 (A1)
addr_2: J1.7, U1.23 (A2)
addr_3: J1.25, U1.22 (A3)
addr_4: J1.6, U1.21 (A4)
addr_5: J1.24, U1.20 (A5)
addr_6: J1.5, U1.19 (A6)
addr_7: J1.23, U1.18 (A7)
addr_8: J1.4, U1.8 (A8)
addr_9: J1.22, U1.7 (A9)
addr_10: J1.3, U1.6 (A10)
addr_11: J1.21, U1.5 (A11)
addr_12: J1.2, U1.4 (A12)
addr_13: J1.20, U1.3 (A13)
addr_14: J1.1, U1.2 (A14)
addr_15: J1.27, R3.1, U1.1 (A15)
addr_16: J1.9, R4.1, U1.48 (A16)
data_0: J1.19, U1.29 (DQ0)
data_1: J1.37, U1.31 (DQ1)
data_2: J1.18, U1.33 (DQ2)
data_3: J1.36, U1.35 (DQ3)
data_4: J1.17, U1.38 (DQ4)
data_5: J1.35, U1.40 (DQ5)
data_6: J1.16, U1.42 (DQ6)
data_7: J1.34, U1.44 (DQ7)
data_8: J1.15, U1.30 (DQ8)
data_9: J1.33, U1.32 (DQ9)
data_10: J1.14, U1.34 (DQ10)
data_11: J1.32, U1.36 (DQ11)
data_12: J1.13, U1.39 (DQ12)
data_13: J1.31, U1.41 (DQ13)
data_14: J1.12, U1.43 (DQ14)
data_15: J1.30, U1.45 (DQ15)

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
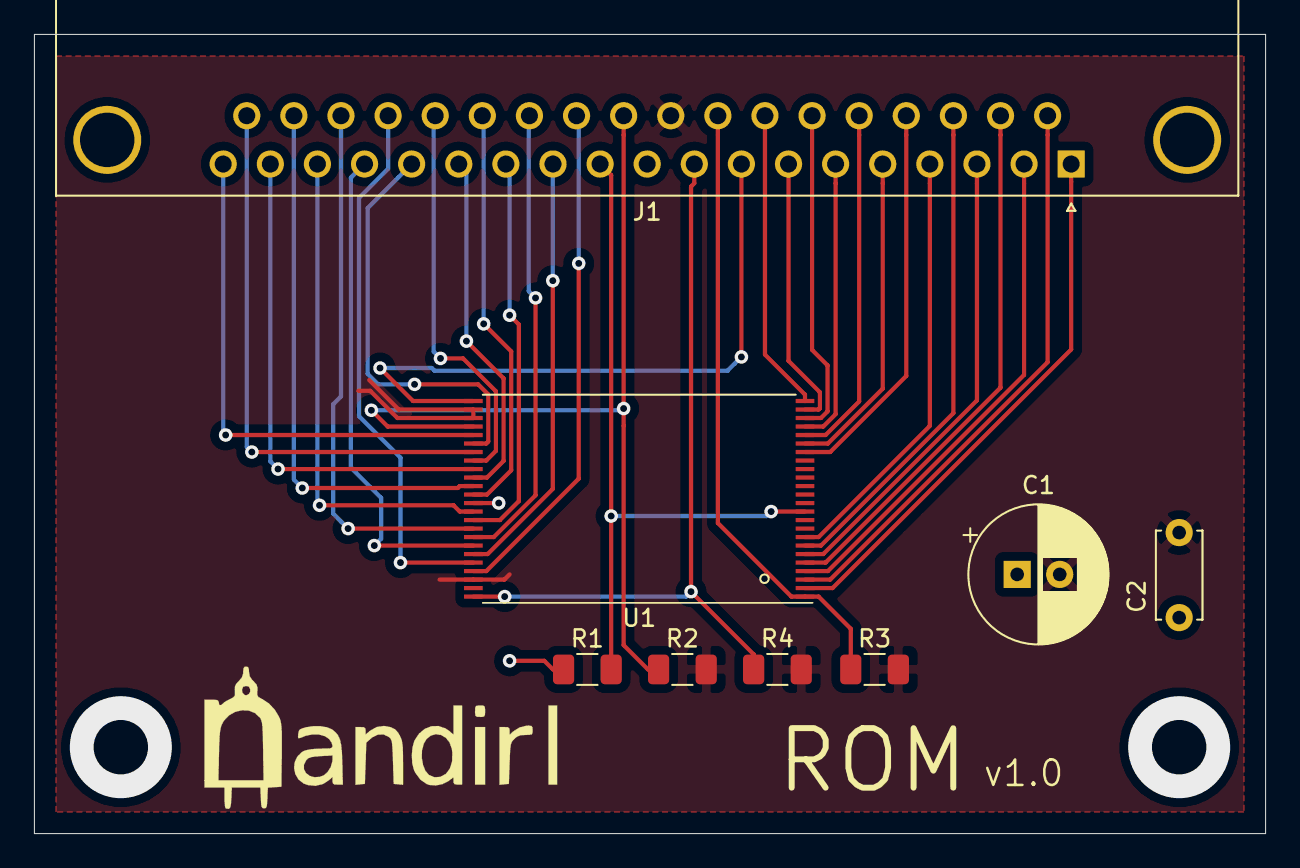
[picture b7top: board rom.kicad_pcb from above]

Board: 2 copper layers, 72.4 x 47.0 mm, 8 parts (0 on the bottom side), 37 nets.
